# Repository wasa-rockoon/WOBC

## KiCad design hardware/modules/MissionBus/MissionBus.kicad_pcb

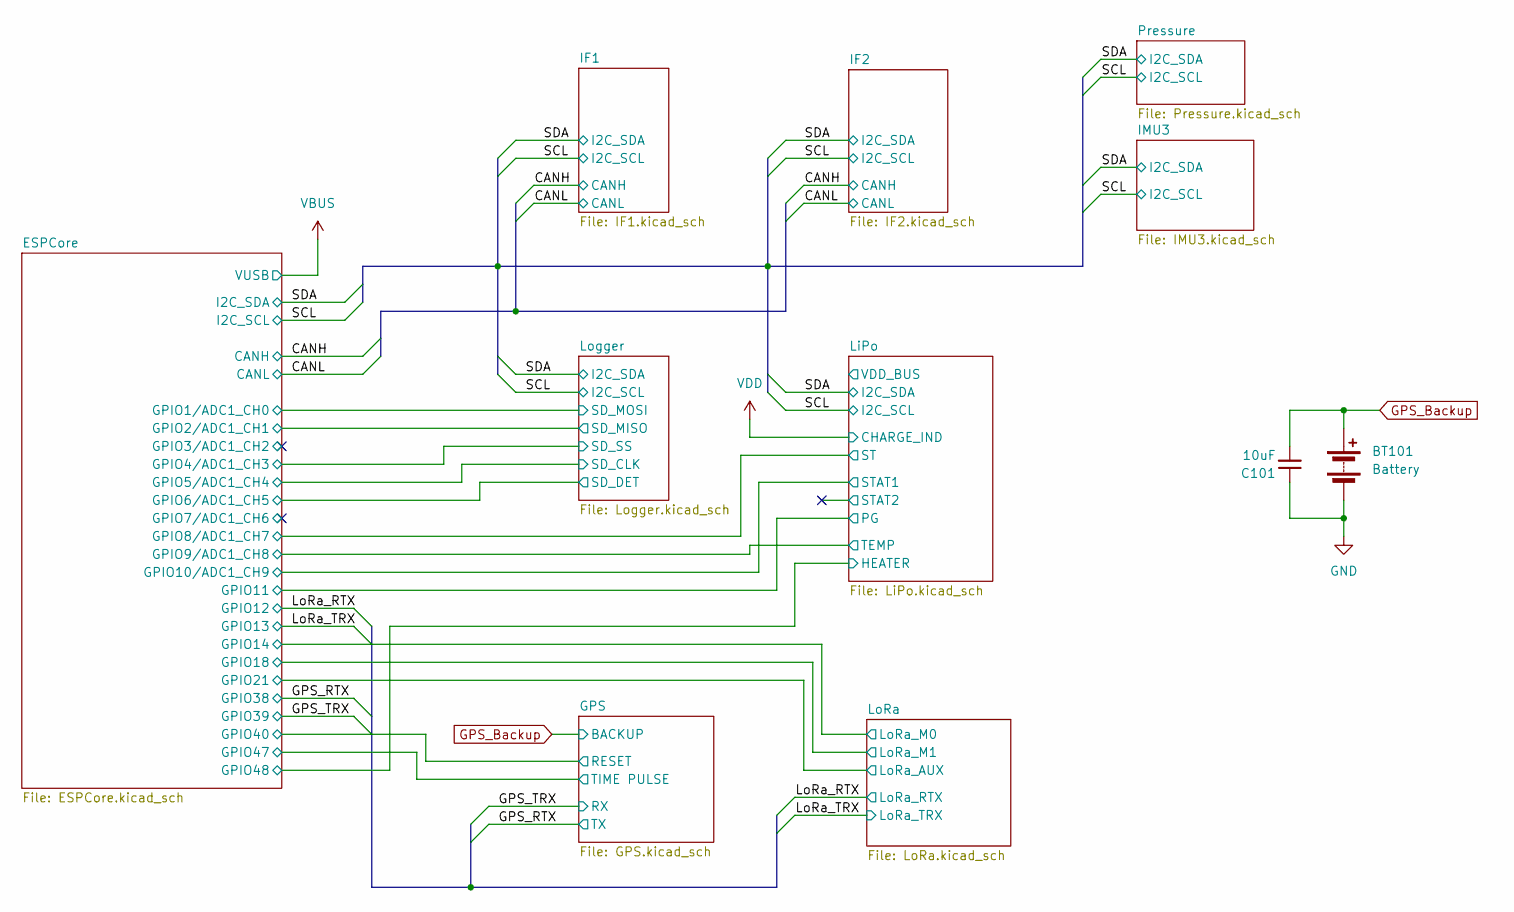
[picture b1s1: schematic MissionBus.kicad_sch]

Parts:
BT101: Battery; cr1220
C101: 10uF; C_0603_1608Metric; LCSC C19702

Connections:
GND: BT101.2 (-), C101.1; also elsewhere on the board
GPS_Backup: BT101.1 (+), C101.2; also elsewhere on the board

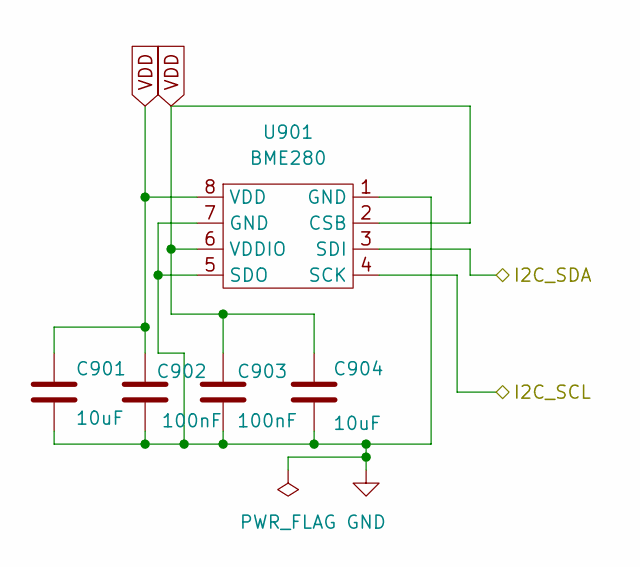
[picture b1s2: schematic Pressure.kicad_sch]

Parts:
C901, C904: 10uF; C_0603_1608Metric; LCSC C19702
C902, C903: 100nF; C_0402_1005Metric; LCSC C1525
U901: BME280; LCSC C92489

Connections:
/SCL: U901.4 (SCK); also elsewhere on the board
/SDA: U901.3 (SDI); also elsewhere on the board
GND: C901.2, C902.2, C903.2, C904.2, U901.1 (GND), U901.5 (SDO), U901.7 (GND); also elsewhere on the board
VDD: C901.1, C902.1, C903.1, C904.1, U901.2 (CSB), U901.6 (VDDIO), U901.8 (VDD); also elsewhere on the board

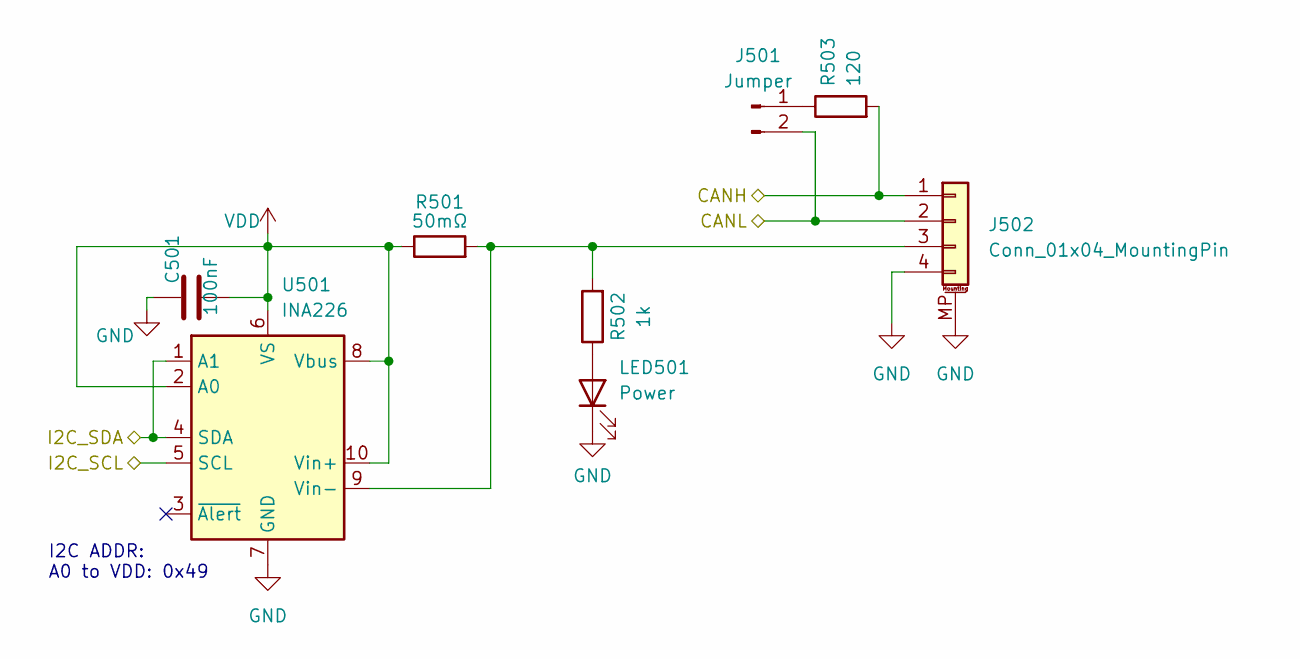
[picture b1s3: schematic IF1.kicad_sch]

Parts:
C501: 100nF; C_0402_1005Metric; LCSC C1525
J501: Jumper; PinHeader_1x02_P1.27mm_Vertical
J502: Conn_01x04_MountingPin; Grove_4P_L_SMD
LED501: Power; LED_0603_1608Metric; LCSC C2297
R501: 50mΩ; R_0805_2012Metric; LCSC C247602
R502: 1k; R_0402_1005Metric; LCSC C11702
R503: 120; R_0402_1005Metric; LCSC C25079
U501: INA226; VSSOP-10_3x3mm_P0.5mm; LCSC C49851

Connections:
/CANH: J502.1, R503.2; also elsewhere on the board
/CANL: J501.2, J502.2; also elsewhere on the board
/SCL: U501.5 (SCL); also elsewhere on the board
/SDA: U501.1 (A1), U501.4 (SDA); also elsewhere on the board
GND: C501.1, J502.4, J502.MP (MountPin), LED501.1 (K), U501.7 (GND); also elsewhere on the board
unnamed: J501.1, R503.1
unnamed: J502.3, R501.2, R502.2, U501.9 (Vin-)
unnamed: LED501.2 (A), R502.1
VDD: C501.2, R501.1, U501.2 (A0), U501.6 (VS), U501.8 (Vbus), U501.10 (Vin+); also elsewhere on the board

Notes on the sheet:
I2C ADDR: A0 to VDD: 0x49

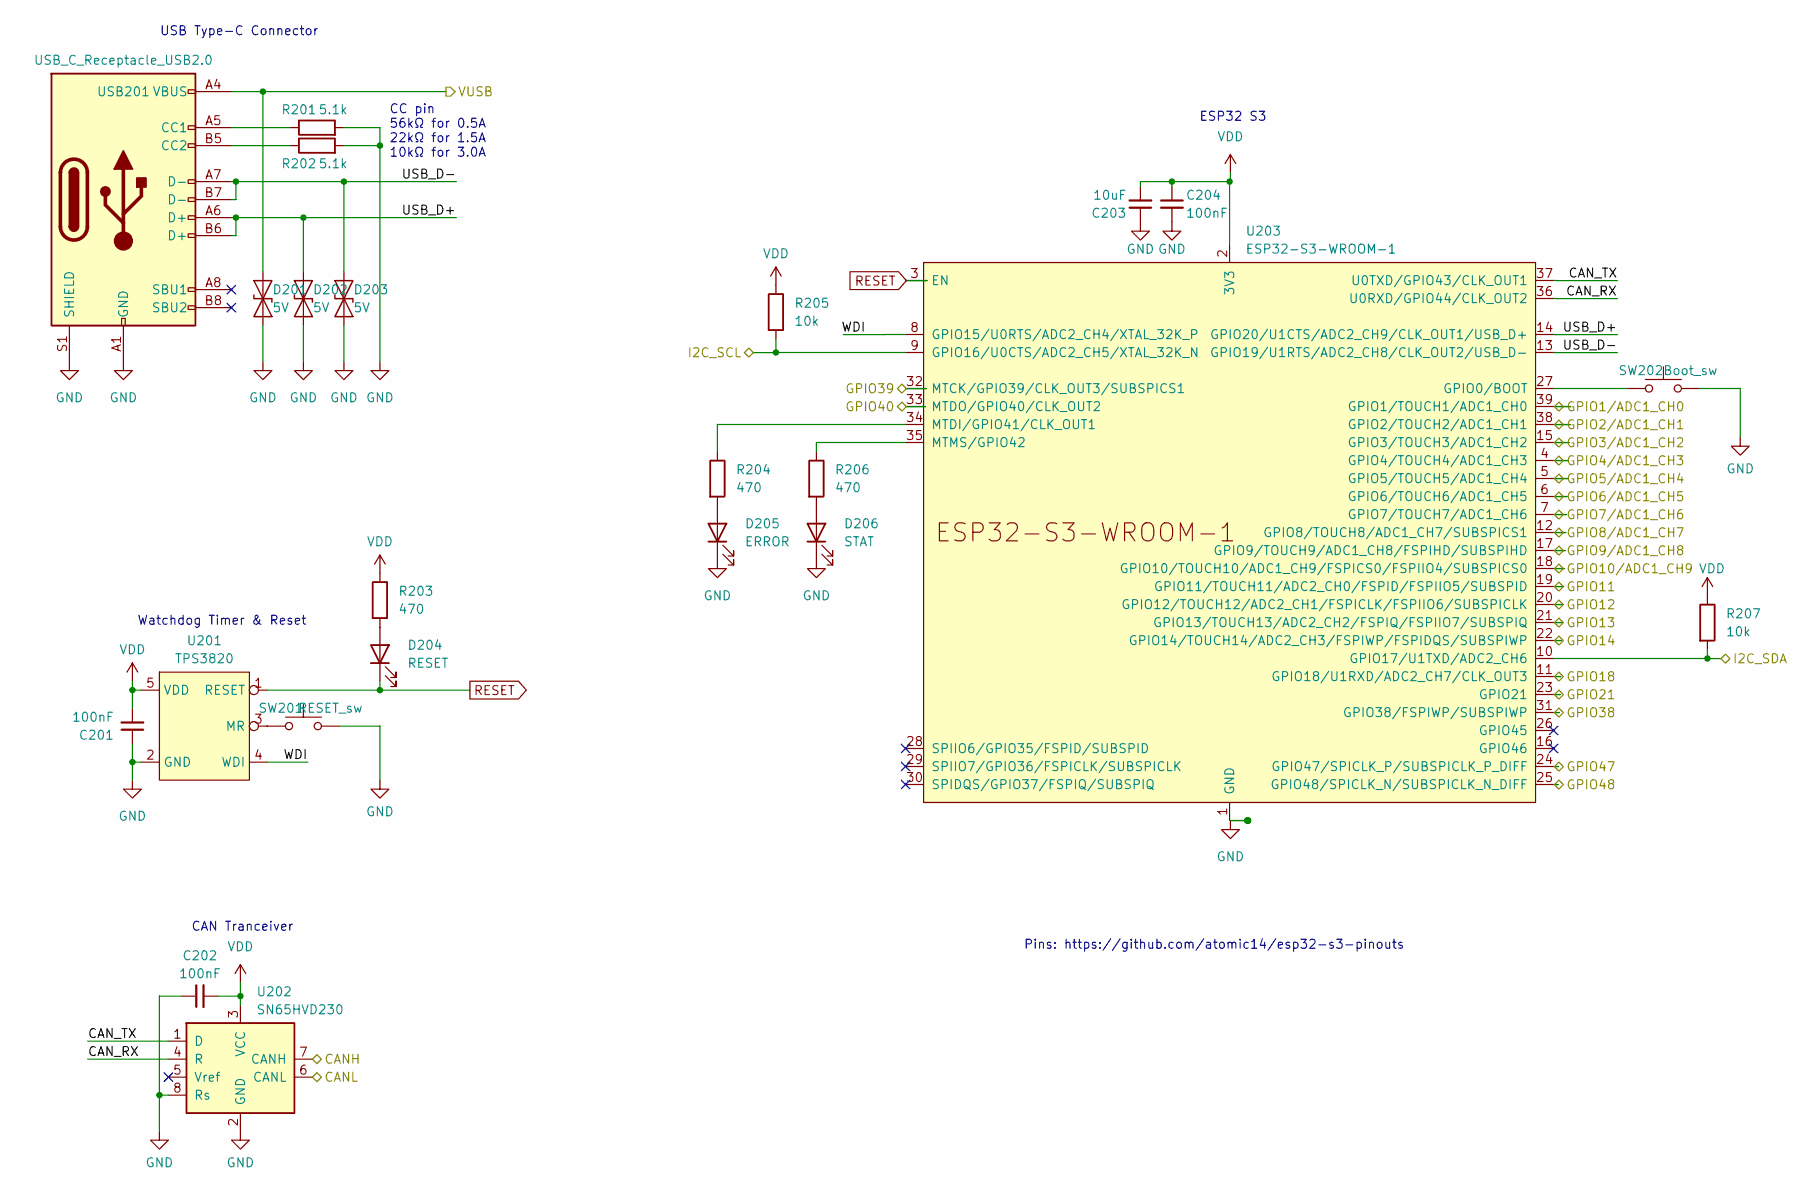
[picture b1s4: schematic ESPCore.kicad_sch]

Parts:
C201, C202, C204: 100nF; C_0402_1005Metric; LCSC C1525
C203: 10uF; C_0603_1608Metric; LCSC C19702
D201, D202, D203: 5V; D_SOD-882; LCSC C7420372
D204: RESET; LED_0805_2012Metric; LCSC C2296
D205: ERROR; LED_0805_2012Metric; LCSC C84256
D206: STAT; LED_0805_2012Metric; LCSC C2297
R201, R202: 5.1k; R_0402_1005Metric; LCSC C25905
R203, R204, R206: 470; R_0402_1005Metric; LCSC C25117
R205, R207: 10k; R_0402_1005Metric; LCSC C25744
SW201: RESET_sw; TVAF06-A020B-R
SW202: Boot_sw; TVAF06-A020B-R
U201: TPS3820; SOT-23-5; LCSC C7719
U202: SN65HVD230; SOIC-8_3.9x4.9mm_P1.27mm; LCSC C12084
U203: ESP32-S3-WROOM-1
USB201: USB_C_Receptacle_USB2.0; USB_C_TYPEC-301S-ACP16X7; LCSC C2856766

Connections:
/CANH: U202.7 (CANH); also elsewhere on the board
/CANL: U202.6 (CANL); also elsewhere on the board
/ESPCore/CAN_RX: U202.4 (R), U203.36 (U0RXD/GPIO44/CLK_OUT2)
/ESPCore/CAN_TX: U202.1 (D), U203.37 (U0TXD/GPIO43/CLK_OUT1)
/ESPCore/GPIO1/ADC1_CH0: U203.39 (GPIO1/TOUCH1/ADC1_CH0); also elsewhere on the board
/ESPCore/GPIO2/ADC1_CH1: U203.38 (GPIO2/TOUCH2/ADC1_CH1); also elsewhere on the board
/ESPCore/GPIO3/ADC1_CH2: U203.15 (GPIO3/TOUCH3/ADC1_CH2)
/ESPCore/GPIO4/ADC1_CH3: U203.4 (GPIO4/TOUCH4/ADC1_CH3); also elsewhere on the board
/ESPCore/GPIO5/ADC1_CH4: U203.5 (GPIO5/TOUCH5/ADC1_CH4); also elsewhere on the board
/ESPCore/GPIO6/ADC1_CH5: U203.6 (GPIO6/TOUCH6/ADC1_CH5); also elsewhere on the board
/ESPCore/GPIO7/ADC1_CH6: U203.7 (GPIO7/TOUCH7/ADC1_CH6)
/ESPCore/GPIO8/ADC1_CH7: U203.12 (GPIO8/TOUCH8/ADC1_CH7/SUBSPICS1); also elsewhere on the board
/ESPCore/GPIO9/ADC1_CH8: U203.17 (GPIO9/TOUCH9/ADC1_CH8/FSPIHD/SUBSPIHD); also elsewhere on the board
/ESPCore/GPIO10/ADC1_CH9: U203.18 (GPIO10/TOUCH10/ADC1_CH9/FSPICS0/FSPIIO4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); also elsewhere on the board
/ESPCore/GPIO11: U203.19 (GPIO11/TOUCH11/ADC2_CH0/FSPID/FSPIIO5/S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); also elsewhere on the board
/ESPCore/GPIO14: U203.22 (GPIO14/TOUCH14/ADC2_CH3/FSPIWP/FSPIDQS/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); also elsewhere on the board
/ESPCore/GPIO18: U203.11 (GPIO18/U1RXD/ADC2_CH7/CLK_OUT3); also elsewhere on the board
/ESPCore/GPIO21: U203.23 (GPIO21); also elsewhere on the board
/ESPCore/GPIO40: U203.33 (MTDO/GPIO40/CLK_OUT2); also elsewhere on the board
/ESPCore/GPIO47: U203.24 (GPIO47/SPICLK_P/SUBSPICLK_P_DIFF); also elsewhere on the board
/ESPCore/GPIO48: U203.25 (GPIO48/SPICLK_N/SUBSPICLK_N_DIFF); also elsewhere on the board
/ESPCore/USB_D+: D202.2 (A2), U203.14 (GPIO20/U1CTS/ADC2_CH9/CLK_OUT1/USB_D+), USB201.A6 (D+), USB201.B6 (D+)
/ESPCore/USB_D-: D203.2 (A2), U203.13 (GPIO19/U1RTS/ADC2_CH8/CLK_OUT2/USB_D-), USB201.A7 (D-), USB201.B7 (D-)
/ESPCore/WDI: U201.4 (WDI), U203.8 (GPIO15/U0RTS/ADC2_CH4/XTAL_32K_P)
/GPS_RTX: U203.31 (GPIO38/FSPIWP/SUBSPIWP); also elsewhere on the board
/GPS_TRX: U203.32 (MTCK/GPIO39/CLK_OUT3/SUBSPICS1); also elsewhere on the board
/LoRa_RTX: U203.20 (GPIO12/TOUCH12/ADC2_CH1/FSPICLK/FSPIIO6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); also elsewhere on the board
/LoRa_TRX: U203.21 (GPIO13/TOUCH13/ADC2_CH2/FSPIQ/FSPIIO7/S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); also elsewhere on the board
/SCL: R205.2, U203.9 (GPIO16/U0CTS/ADC2_CH5/XTAL_32K_N); also elsewhere on the board
/SDA: R207.2, U203.10 (GPIO17/U1TXD/ADC2_CH6); also elsewhere on the board
GND: C201.1, C202.1, C203.1, C204.2, D201.1 (A1), D202.1 (A1), D203.1 (A1), D205.1 (K), D206.1 (K), R201.2, R202.2, SW201.2, SW202.2, U201.2 (GND), U202.2 (GND), U202.8 (Rs), U203.1 (GND), U203.40 (GND), U203.41 (GND), USB201.A1 (GND), USB201.A12 (GND), USB201.B1 (GND), USB201.B12 (GND), USB201.S1 (SHIELD); also elsewhere on the board
unnamed: D204.2 (A), R203.2
unnamed: D205.2 (A), R204.2
unnamed: D206.2 (A), R206.2
unnamed: SW201.1, U201.3 (MR)
unnamed: SW202.1, U203.27 (GPIO0/BOOT)
unnamed: R204.1, U203.34 (MTDI/GPIO41/CLK_OUT1)
unnamed: R206.1, U203.35 (MTMS/GPIO42)
unnamed: R201.1, USB201.A5 (CC1)
unnamed: R202.1, USB201.B5 (CC2)
RESET: D204.1 (K), U201.1 (RESET), U203.3 (EN)
VBUS: D201.2 (A2), USB201.A4 (VBUS), USB201.A9 (VBUS), USB201.B4 (VBUS), USB201.B9 (VBUS); also elsewhere on the board
VDD: C201.2, C202.2, C203.2, C204.1, R203.1, R205.1, R207.1, U201.5 (VDD), U202.3 (VCC), U203.2 (3V3); also elsewhere on the board

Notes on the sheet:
USB Type-C Connector
CC pin 56kΩ for 0.5A 22kΩ for 1.5A 10kΩ for 3.0A
Watchdog Timer & Reset
ESP32 S3
Pins: https://github.com/atomic14/esp32-s3-pinouts
CAN Tranceiver

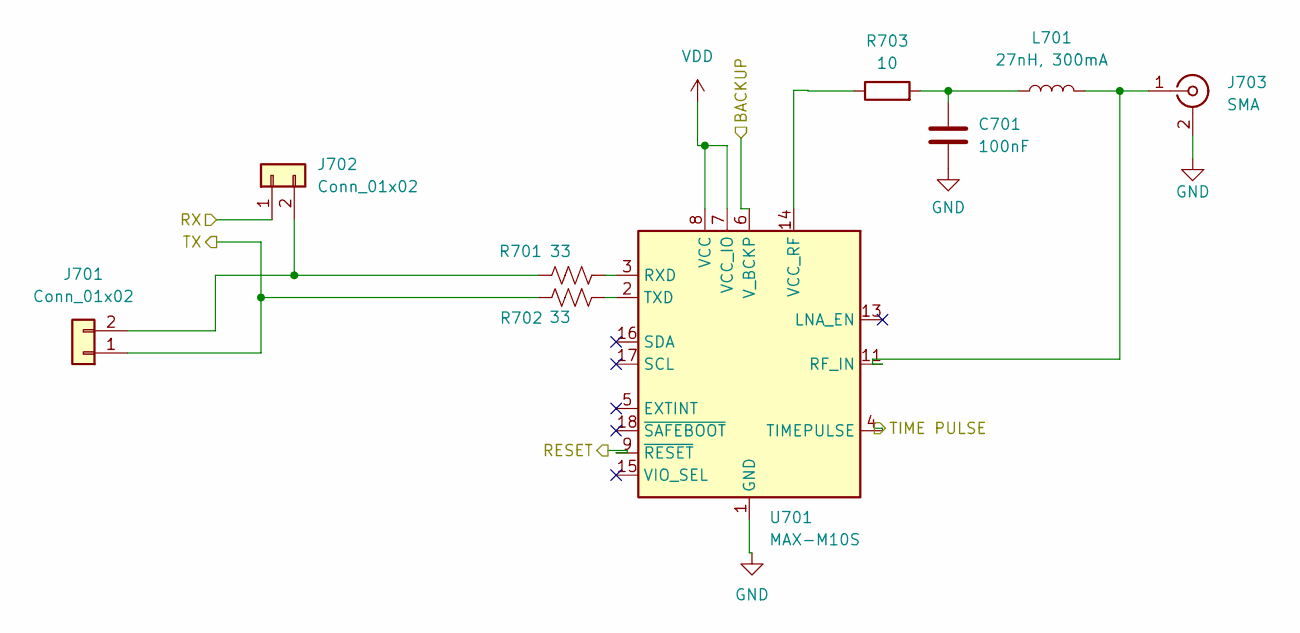
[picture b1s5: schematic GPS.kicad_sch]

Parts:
C701: 100nF; C_0402_1005Metric; LCSC C1525
J701, J702: Conn_01x02; PinHeader_1x02_P1.27mm_Vertical
J703: SMA; SMA_Amphenol_132203-12_Horizontal; LCSC C2693813
L701: 27nH, 300mA; L_0402_1005Metric; LCSC C18830
R701, R702: 33; R_0402_1005Metric; LCSC C25077
R703: 10; R_0402_1005Metric; LCSC C25077
U701: MAX-M10S; ublox_MAX

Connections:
/ESPCore/GPIO40: U701.9 (~RESET); also elsewhere on the board
/ESPCore/GPIO47: U701.4 (TIMEPULSE); also elsewhere on the board
/GPS_RTX: J701.1, R702.2; also elsewhere on the board
/GPS_TRX: J702.1; also elsewhere on the board
GND: C701.2, J703.2 (Ext), U701.1 (GND), U701.10 (GND), U701.12 (GND); also elsewhere on the board
GPS_Backup: U701.6 (V_BCKP); also elsewhere on the board
unnamed: C701.1, L701.1, R703.2
unnamed: J701.2, J702.2, R701.2
unnamed: J703.1 (In), L701.2, U701.11 (RF_IN)
unnamed: R701.1, U701.3 (RXD)
unnamed: R702.1, U701.2 (TXD)
unnamed: R703.1, U701.14 (VCC_RF)
VDD: U701.7 (VCC_IO), U701.8 (VCC); also elsewhere on the board

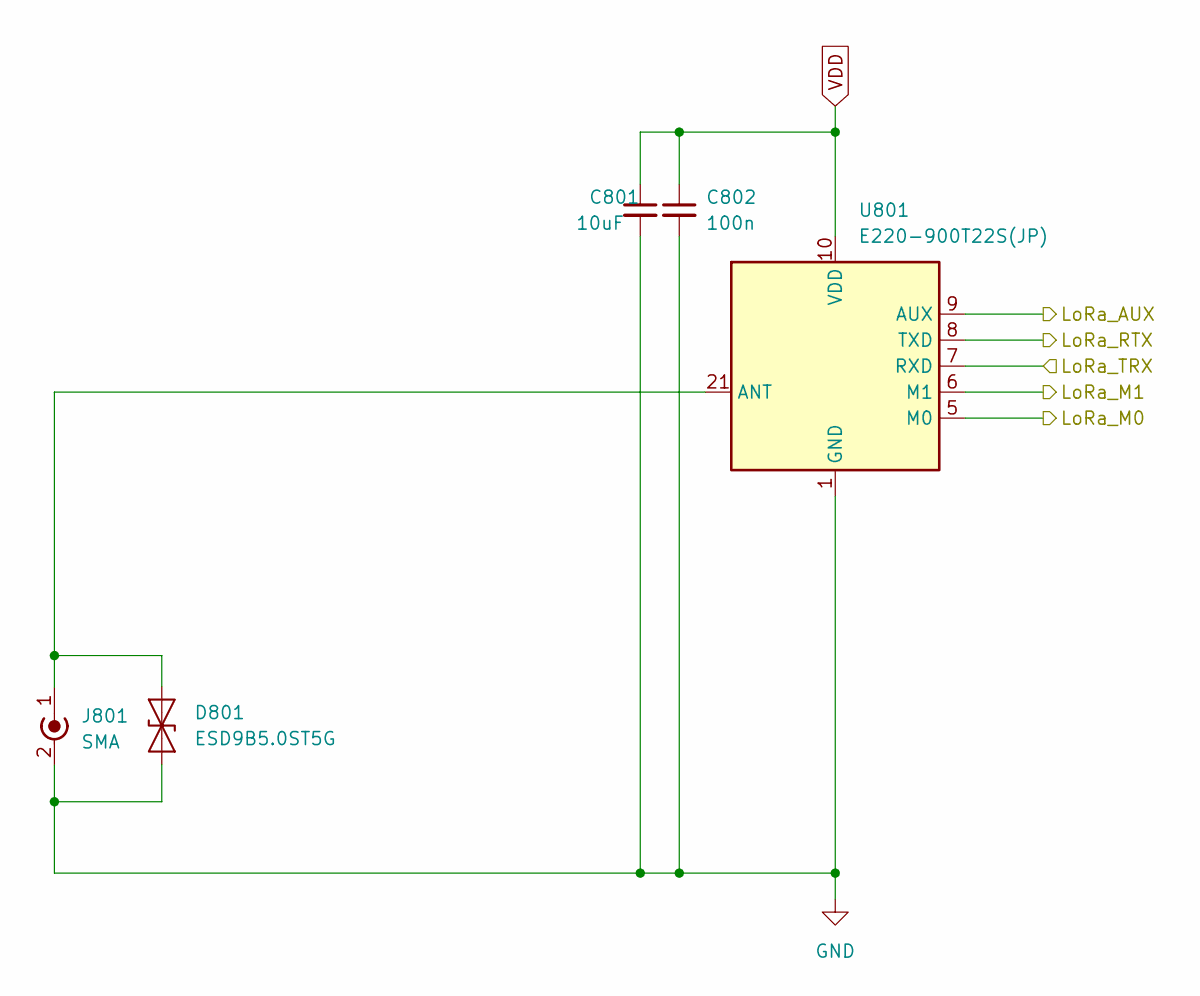
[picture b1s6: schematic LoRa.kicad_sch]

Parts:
C801: 10uF; C_0603_1608Metric; LCSC C19702
C802: 100n; C_0402_1005Metric; LCSC C1525
D801: ESD9B5.0ST5G; D_SOD-882; LCSC C7420372
J801: SMA; SMA_Amphenol_132203-12_Horizontal; LCSC C2693813
U801: E220-900T22S(JP)

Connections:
/ESPCore/GPIO14: U801.5 (M0); also elsewhere on the board
/ESPCore/GPIO18: U801.6 (M1); also elsewhere on the board
/ESPCore/GPIO21: U801.9 (AUX); also elsewhere on the board
/LoRa_RTX: U801.8 (TXD); also elsewhere on the board
/LoRa_TRX: U801.7 (RXD); also elsewhere on the board
GND: C801.2, C802.2, D801.1 (A1), J801.2 (Ext), U801.1 (GND), U801.2 (GND), U801.3 (GND), U801.4 (GND), U801.11 (GND), U801.13 (GND), U801.19 (GND), U801.20 (GND), U801.22 (GND); also elsewhere on the board
unnamed: D801.2 (A2), J801.1 (In), U801.21 (ANT)
VDD: C801.1, C802.1, U801.10 (VDD); also elsewhere on the board

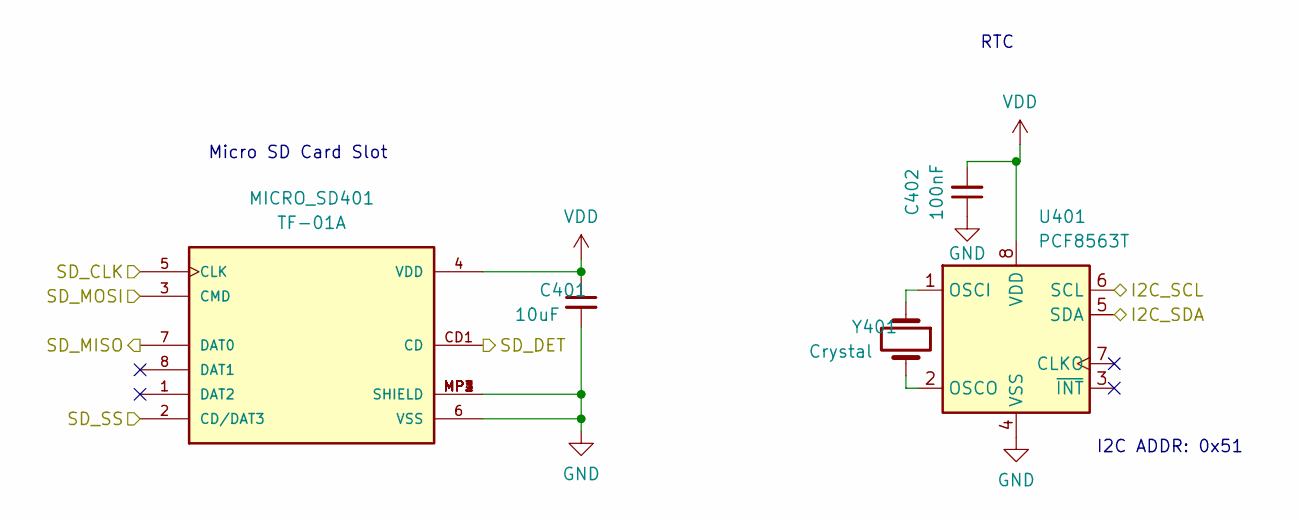
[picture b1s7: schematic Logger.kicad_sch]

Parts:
C401: 10uF; C_0603_1608Metric; LCSC C19702
C402: 100nF; C_0402_1005Metric; LCSC C1525
MICRO_SD401: TF-01A; LCSC C5155563
U401: PCF8563T; SOIC-8_3.9x4.9mm_P1.27mm; LCSC C7440
Y401: Crystal; Crystal_SMD_3215-2Pin_3.2x1.5mm; LCSC C32346

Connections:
/ESPCore/GPIO1/ADC1_CH0: MICRO_SD401.3 (CMD); also elsewhere on the board
/ESPCore/GPIO2/ADC1_CH1: MICRO_SD401.7 (DAT0); also elsewhere on the board
/ESPCore/GPIO4/ADC1_CH3: MICRO_SD401.2 (CD/DAT3); also elsewhere on the board
/ESPCore/GPIO5/ADC1_CH4: MICRO_SD401.5 (CLK); also elsewhere on the board
/ESPCore/GPIO6/ADC1_CH5: MICRO_SD401.CD1 (CD); also elsewhere on the board
/SCL: U401.6 (SCL); also elsewhere on the board
/SDA: U401.5 (SDA); also elsewhere on the board
GND: C401.2, C402.1, MICRO_SD401.6 (VSS), MICRO_SD401.MP1 (SHIELD), MICRO_SD401.MP2 (SHIELD), MICRO_SD401.MP3 (SHIELD), MICRO_SD401.MP4 (SHIELD), U401.4 (VSS); also elsewhere on the board
unnamed: U401.1 (OSCI), Y401.1
unnamed: U401.2 (OSCO), Y401.2
VDD: C401.1, C402.2, MICRO_SD401.4 (VDD), U401.8 (VDD); also elsewhere on the board

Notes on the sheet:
I2C ADDR: 0x51
RTC
Micro SD Card Slot

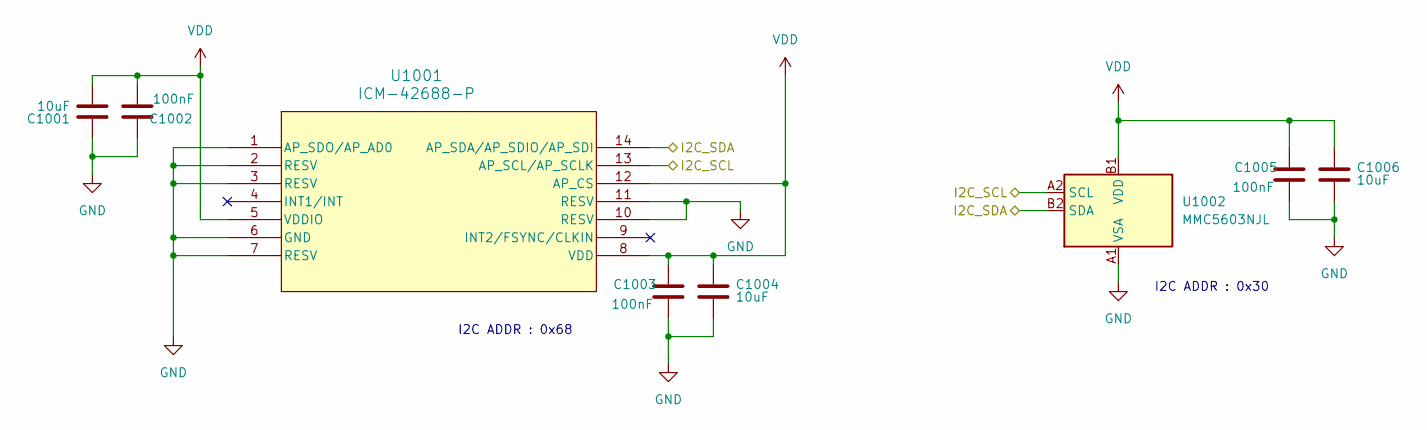
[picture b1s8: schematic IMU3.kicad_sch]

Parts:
C1001, C1004, C1006: 10uF; C_0603_1608Metric; LCSC C19702
C1002, C1003, C1005: 100nF; C_0402_1005Metric; LCSC C1525
U1001: ICM-42688-P; LGA-14_3x2.5mm_P0.5mm_LayoutBorder3x4y; LCSC C1850418
U1002: MMC5603NJL; WLP4_0P82X0P82_MEM-L; LCSC C404328

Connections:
/SCL: U1001.13 (AP_SCL/AP_SCLK), U1002.A2 (SCL); also elsewhere on the board
/SDA: U1001.14 (AP_SDA/AP_SDIO/AP_SDI), U1002.B2 (SDA); also elsewhere on the board
GND: C1001.1, C1002.1, C1003.2, C1004.2, C1005.2, C1006.2, U1001.1 (AP_SDO/AP_AD0), U1001.2 (RESV), U1001.3 (RESV), U1001.6 (GND), U1001.7 (RESV), U1001.10 (RESV), U1001.11 (RESV), U1002.A1 (VSA); also elsewhere on the board
VDD: C1001.2, C1002.2, C1003.1, C1004.1, C1005.1, C1006.1, U1001.5 (VDDIO), U1001.8 (VDD), U1001.12 (AP_CS), U1002.B1 (VDD); also elsewhere on the board

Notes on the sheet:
I2C ADDR : 0x30
I2C ADDR : 0x68

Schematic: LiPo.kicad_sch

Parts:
C301, C302, C303, C305, C306, C310, C312: 10uF; C_0603_1608Metric; LCSC C19702
C304, C309, C311, C316: 100nF; C_0402_1005Metric; LCSC C1525
C307, C308, C313, C314, C315: 22uF; C_0805_2012Metric; LCSC C45783
F301, F302, F303: Polyfuse; Fuse_1206_3216Metric; LCSC C883133
J301: Battery; JST_XH_S2B-XH-A_1x02_P2.50mm_Horizontal
J302: Temp&Heater; JST_PH_S3B-PH-K_1x03_P2.00mm_Horizontal
J303: Ext Switch; JST_PH_S2B-PH-K_1x02_P2.00mm_Horizontal
J304: Conn_01x02; PinHeader_1x02_P1.27mm_Vertical
J305: LiPo; JST_PH_S2B-PH-K_1x02_P2.00mm_Horizontal
L301: L; L_Wuerth_WE-TPC-3816; LCSC C3033018
LED301: USB Power; LED_0805_2012Metric; LCSC C2297
LED302: CHARGE; LED_0805_2012Metric; LCSC C2296
LED303: Backup; LED_0805_2012Metric; LCSC C2296
LED304: Heater; LED_0805_2012Metric; LCSC C2296
LED305: VDD; LED_0805_2012Metric; LCSC C2297
Q301: Q_NPN_BEC; SOT-23; LCSC C20526
Q302: Q_PMOS_GSD; SOT-23; LCSC C15127
R301, R302, R303, R309, R312, R322: 1k; R_0402_1005Metric; LCSC C11702
R304, R305, R307, R310, R318: 100k; R_0402_1005Metric; LCSC C25741
R306, R320: 47k; R_0402_1005Metric; LCSC C25792
R308, R311, R314, R315: 10k; R_0402_1005Metric; LCSC C25744
R313, R317, R321: 50mΩ; R_0805_2012Metric; LCSC C247602
R316: 330k; R_0402_1005Metric; LCSC C25778
R319: 15k; R_0402_1005Metric; LCSC C25756
RV301: 10k; Potentiometer_Bourns_TC33X_Vertical; LCSC C719176
U301: MCP73871-1CC; QFN-20-1EP_4x4mm_P0.5mm_EP2.5x2.5mm; LCSC C511310
U302: TPS2116DRL; SOT-583-8
U303, U304, U306: INA226; VSSOP-10_3x3mm_P0.5mm; LCSC C49851
U305: TPS63070RNMR; VREG_TPS63070RNMR; LCSC C109322

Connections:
/ESPCore/GPIO8/ADC1_CH7: R309.2, U302.8 (ST); also elsewhere on the board
/ESPCore/GPIO9/ADC1_CH8: J302.2, J304.1, U301.5 (THERM); also elsewhere on the board
/ESPCore/GPIO10/ADC1_CH9: LED302.1 (K), U301.8 (STAT1/~LBO); also elsewhere on the board
/ESPCore/GPIO11: U301.6 (~PG); also elsewhere on the board
/ESPCore/GPIO48: R308.2; also elsewhere on the board
/LiPo/PROG: RV301.2, U301.13 (PROG1)
/LiPo/STAT2: U301.7 (STAT2)
/LiPo/VDD_BUS: C312.1, C313.1, C314.1, C315.1, C316.1, R318.1, R320.2, R321.1, U305.7_8 (VOUT), U306.6 (VS), U306.8 (Vbus), U306.10 (Vin+)
/SCL: U303.1 (A1), U303.5 (SCL), U304.1 (A1), U304.2 (A0), U304.5 (SCL), U306.1 (A1), U306.5 (SCL); also elsewhere on the board
/SDA: U303.4 (SDA), U304.4 (SDA), U306.2 (A0), U306.4 (SDA); also elsewhere on the board
GND: C301.2, C302.2, C303.2, C304.2, C305.2, C306.2, C307.2, C308.2, C309.2, C310.2, C311.2, C312.2, C313.2, C314.2, C315.2, C316.2, J301.2, J302.3, J305.2, Q301.2 (E), R301.2, R303.2, R304.2, R306.1, R310.2, R312.1, R315.2, R316.2, R319.1, R322.2, U301.9 (~TE), U301.10 (V_{SS}), U301.11 (V_{SS}), U301.21 (V_{SS}), U302.1 (GND), U303.7 (GND), U304.7 (GND), U305.4 (GND), U305.10 (PGND), U305.15 (VSEL), U306.7 (GND); also elsewhere on the board
unnamed: F302.1, J301.1
unnamed: J302.1, LED304.2 (A), Q302.3 (D)
unnamed: J303.1, R314.1
unnamed: J303.2, R316.1, U303.3 (~Alert), U305.1 (PS/SYNC), U305.14 (EN), U306.3 (~Alert)
unnamed: J304.2, R315.1
unnamed: F303.2, J305.1
unnamed: C301.1, F301.2, LED301.2 (A), R305.1, U301.2 (VPCC), U301.3 (SEL), U301.18 (IN), U301.19 (IN)
unnamed: LED301.1 (K), R301.1
unnamed: LED302.2 (A), R302.1
unnamed: LED303.1 (K), R309.1
unnamed: LED304.1 (K), R312.2
unnamed: LED305.1 (K), R322.1
unnamed: Q301.1 (B), R308.1, R310.1
unnamed: Q301.3 (C), Q302.1 (G), R311.2
unnamed: R303.1, RV301.3
unnamed: R305.2, U301.17 (CE), U304.3 (~Alert)
unnamed: R304.1, U301.12 (PROG3)
unnamed: C306.1, R317.1, U301.14 (V_{BAT}), U301.15 (V_{BAT}), U301.16 (V_{BAT_SENSE}), U304.9 (Vin-)
unnamed: C303.1, C305.1, R307.1, U301.1 (OUT), U301.20 (OUT), U302.3 (VIN1), U302.5 (MODE)
unnamed: R306.2, R307.2, U302.4 (PR1)
unnamed: C302.1, F302.2, U302.6 (VIN2)
unnamed: C307.1, C308.1, C310.1, R313.2, R314.2, U303.9 (Vin-), U305.12_13 (VIN)
unnamed: F303.1, R317.2, U304.8 (Vbus), U304.10 (Vin+)
unnamed: R319.2, R320.1, U305.5 (FB)
unnamed: L301.1, U305.11 (L1)
unnamed: L301.2, U305.9 (L2)
unnamed: R318.2, U305.2 (PG)
unnamed: C311.1, U305.3 (VAUX)
VBUS: F301.1; also elsewhere on the board
VDD: LED305.2 (A), R302.2, R321.2, U306.9 (Vin-); also elsewhere on the board
VPP: C304.1, C309.1, LED303.2 (A), Q302.2 (S), R311.1, R313.1, U302.2 (VOUT), U302.7 (VOUT), U303.2 (A0), U303.6 (VS), U303.8 (Vbus), U303.10 (Vin+), U304.6 (VS)

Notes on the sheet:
6V Max
I2C ADDR: 0x4D
-> 3.3V Output
Backup Battery ->
USB Bus Power ->
I2C ADDR: 0x4E
<-> LiPo
I2C ADDR: 0x4F

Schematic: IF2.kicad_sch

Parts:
C601: 100nF; C_0402_1005Metric; LCSC C1525
J601: Jumper; PinHeader_1x02_P1.27mm_Vertical
J602: Conn_01x04_MountingPin; Grove_4P_L_SMD
LED601: Power; LED_0603_1608Metric; LCSC C2297
R601: 50mΩ; R_0805_2012Metric; LCSC C247602
R602: 1k; R_0402_1005Metric; LCSC C11702
R603: 120; R_0402_1005Metric; LCSC C25079
U601: INA226; VSSOP-10_3x3mm_P0.5mm; LCSC C49851

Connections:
/CANH: J602.1, R603.2; also elsewhere on the board
/CANL: J601.2, J602.2; also elsewhere on the board
/SCL: U601.5 (SCL); also elsewhere on the board
/SDA: U601.1 (A1), U601.4 (SDA); also elsewhere on the board
GND: C601.1, J602.4, J602.MP (MountPin), LED601.1 (K), U601.7 (GND); also elsewhere on the board
unnamed: J601.1, R603.1
unnamed: J602.3, R601.2, R602.2, U601.9 (Vin-)
unnamed: LED601.2 (A), R602.1
VDD: C601.2, R601.1, U601.2 (A0), U601.6 (VS), U601.8 (Vbus), U601.10 (Vin+); also elsewhere on the board

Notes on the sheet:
I2C ADDR: A0 to GND: 0x48

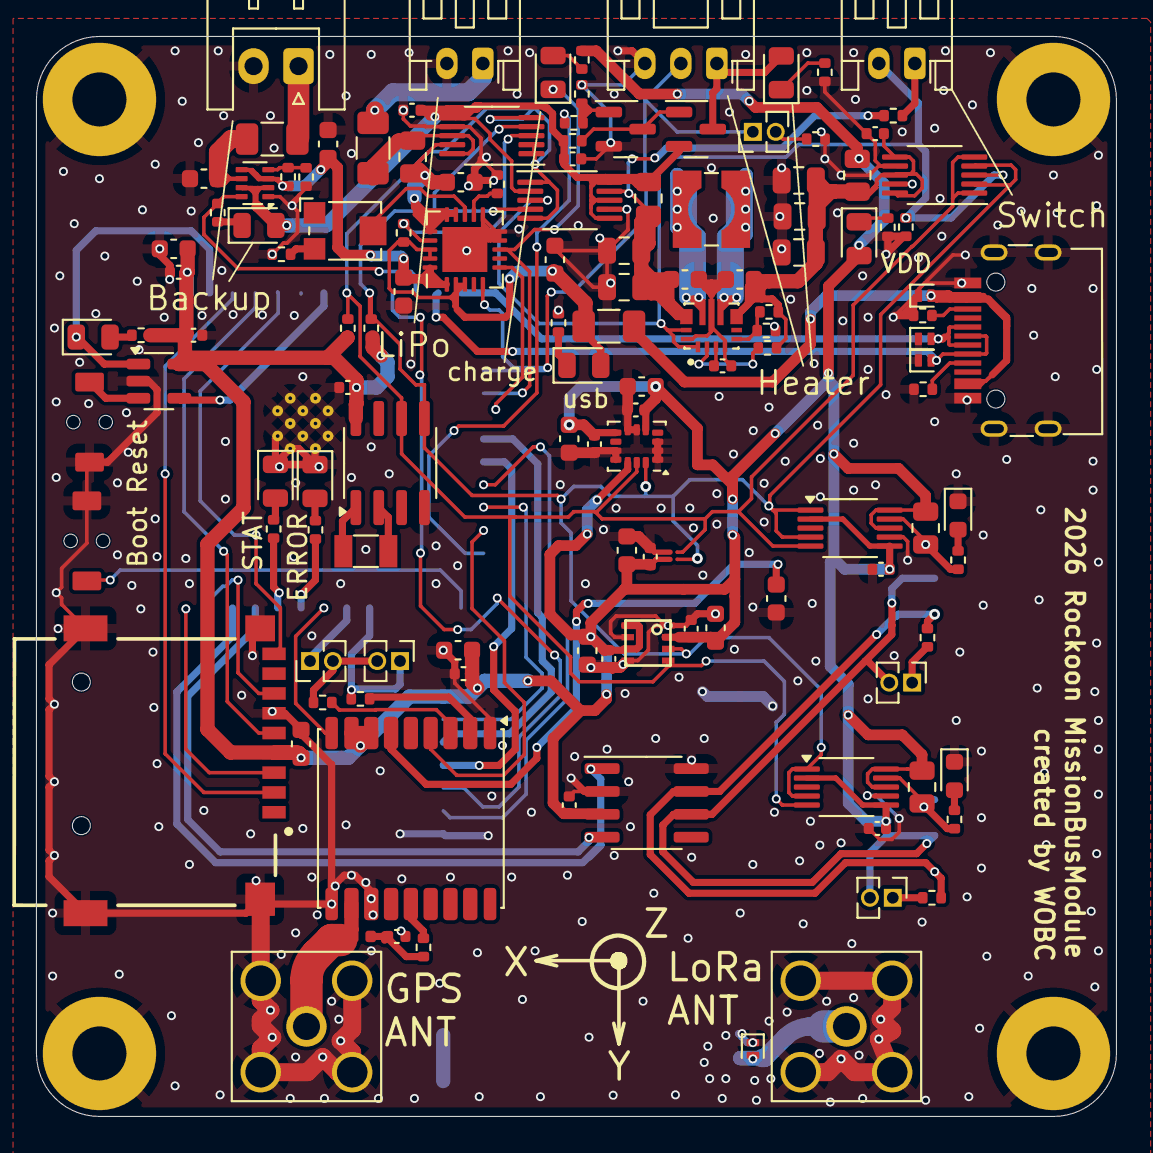
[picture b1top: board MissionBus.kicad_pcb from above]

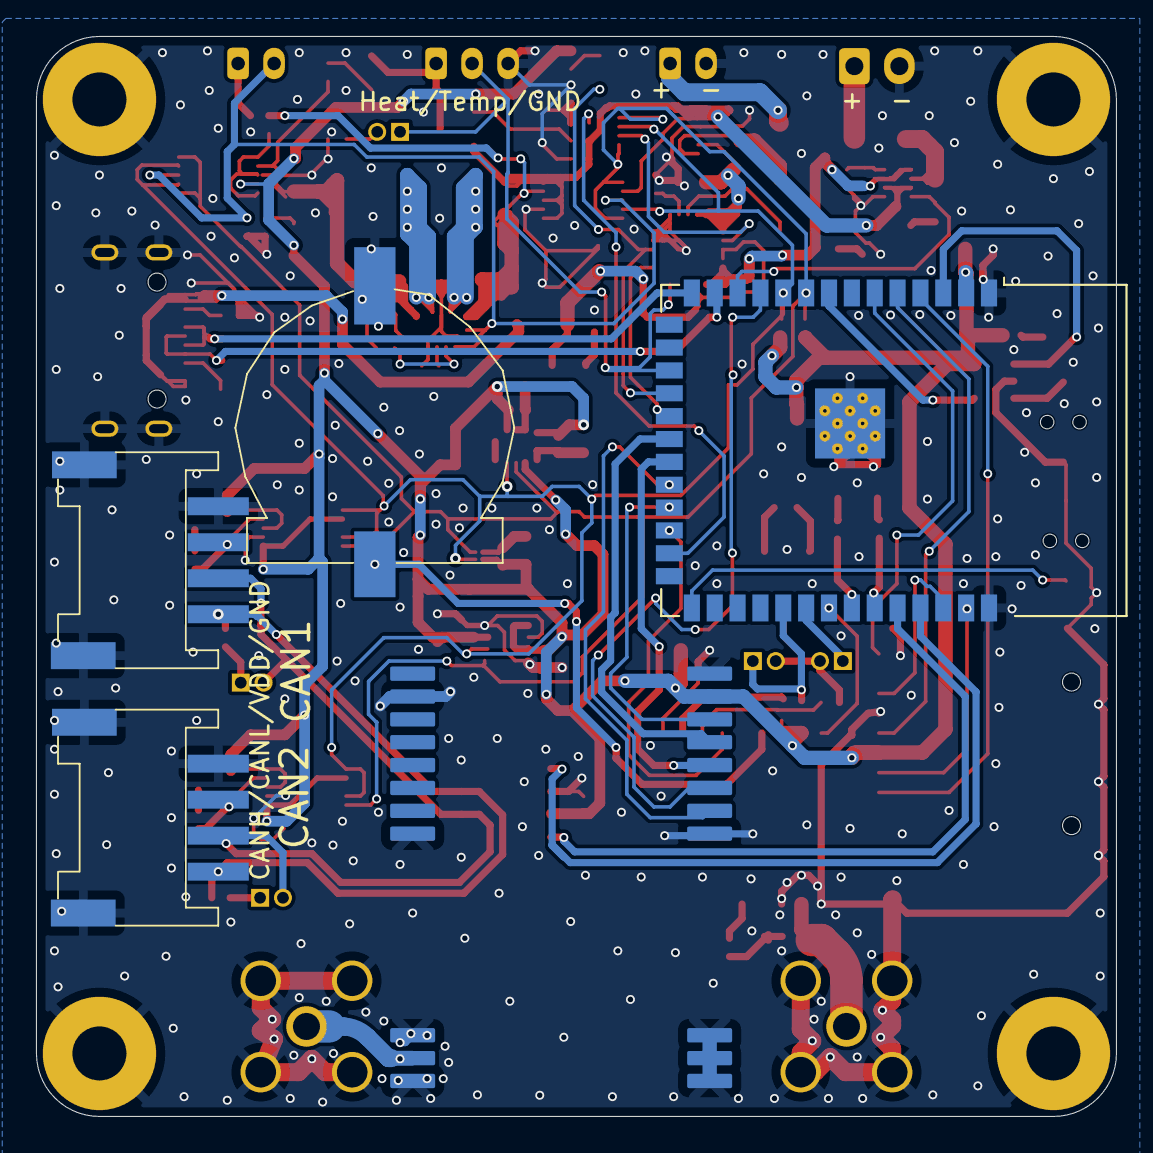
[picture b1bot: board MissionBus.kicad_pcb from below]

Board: 2 copper layers, 60.0 x 60.0 mm, 134 parts (5 on the bottom side), 88 nets.
